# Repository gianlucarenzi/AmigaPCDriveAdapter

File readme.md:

# Amiga Floppy to PC Floppy Adapter

Created by Gianluca Renzi (C) 2018
 E-Mail:
- <icjtqr@gmail.com>
- <gianlucarenzi@eurek.it>

# PCB Revision History

- V0.1 Initial Revision 2018 Made with Kicad 4.x
- V1.0 First (BAD) PCB revision from transition from Kicad 4.x to Kicad 5.x
- V2.0 PCB Revision entirely made on Kicad 5. No library from Kicad 4 anymore.

# What is it?
It is a simple but powerful adapter to use internally in any Amiga Computer!
It must be connected to the floppy disk drive 34-pin interface on the drive
itself, then hooked up with the original cables from Amiga motherboard.

# Images

# What's changed?

- V0.1 Initial release (2018)
- V1.0 From Kicad 4 to Kicad 5 (2019). I found a bug in PCB version automatically generated by Kicad 5 from Kicad 4: All the hand soldering pads are way too large and they are overlapping each other short-circuiting every signal with a large series of resistors. Thanks to: __Stefan Gammelgaard(BM)__ to point me out on this issue.
- V2.0 Updated and Corrected for usage in Kicad 5 (2020)

# Bill of materials (from Digikey)

| Quantity | Digikey's Part No.           | Manufacturer's Part. No. | Description                   | PCB/Schematic's Reference   |
| -------- | -----------------------------| ------------------------ | ----------------------------- | --------------------------- |
|    2     | 445-10000-1-ND	              | CGA5H2X8R2A104K115AD	    | CAP CER 0.1UF 100V 1206 EPOXY |          C2, C3             |
|   10	    | P2.2KECT-ND	                 | ERJ-8GEYJ222V	           | RES SMD 2.2K OHM 5% 1/4W 1206 | R1, R2, R3, R4, R5, R6, R7  |
|    1	    | 754-APTR3216SECK/J3-PRVCT-ND | APTR3216SECK/J3-PRV	     | LED SMD	                      |             D1              |
|    1     | WM4002-ND                    |	0022032041	              | CONN HEADER VERT 4POS 2.54MM	 |             P1              |
|    1     | 609-3407-ND                  | 68016-404HLF             | CONN HEADER R/A 4POS 2.54MM   |             P2              |
|    1     | 541-CRCW1206330RJNEACCT-ND   | CRCW1206330RJNEAC        | RES 330 OHM 5% 1/4W 1206      |             R8              |
|    1     | S9174-ND                     | SBH11-PBPC-D17-ST-BK     | CONN HEADER VERT 34POS 2.54MM |          TO_AMIGA1          |
|    1     | ED3068-ND                    | SH2-34G-PT               | CONN RCPT 34POS 0.1 GOLD PCB  |          TO_FLOPPY1         |
|    1     | 296-1664-5-ND                | SN74LS38N                | IC GATE NAND 4CH 2-INP 14DIP  |             U1              |
|    2     | 478-10757-1-ND               | TPSA106K016R1000         | CAP TANT 10UF 10% 16V 1206    |           C1, C4            |

# Licence
This entire project is available under the GNU General Public License v3 licence.
See licence.txt for more details.

Additional Copyright/License
Permission is hereby granted, free of charge, to any person obtaining a copy of this software and associated documentation files (the "Software"), to deal in the Software without restriction, including without limitation the rights to use, copy, modify, merge, publish, distribute, sublicense, and/or sell copies of the Software, and to permit persons to whom the Software is furnished to do so, subject to the following conditions:

The above copyright notice and this permission notice shall be included in all copies or substantial portions of the Software/Hardware.

THE SOFTWARE/HARDWARE IS PROVIDED "AS IS", WITHOUT WARRANTY OF ANY KIND, EXPRESS OR IMPLIED, INCLUDING BUT NOT LIMITED TO THE WARRANTIES OF MERCHANTABILITY, FITNESS FOR A PARTICULAR PURPOSE AND NONINFRINGEMENT. IN NO EVENT SHALL THE AUTHORS OR COPYRIGHT HOLDERS BE LIABLE FOR ANY CLAIM, DAMAGES OR OTHER LIABILITY, WHETHER IN AN ACTION OF CONTRACT, TORT OR OTHERWISE, ARISING FROM, OUT OF OR IN CONNECTION WITH THE SOFTWARE/HARDWARE OR THE USE OR OTHER DEALINGS IN THE SOFTWARE/HARDWARE.

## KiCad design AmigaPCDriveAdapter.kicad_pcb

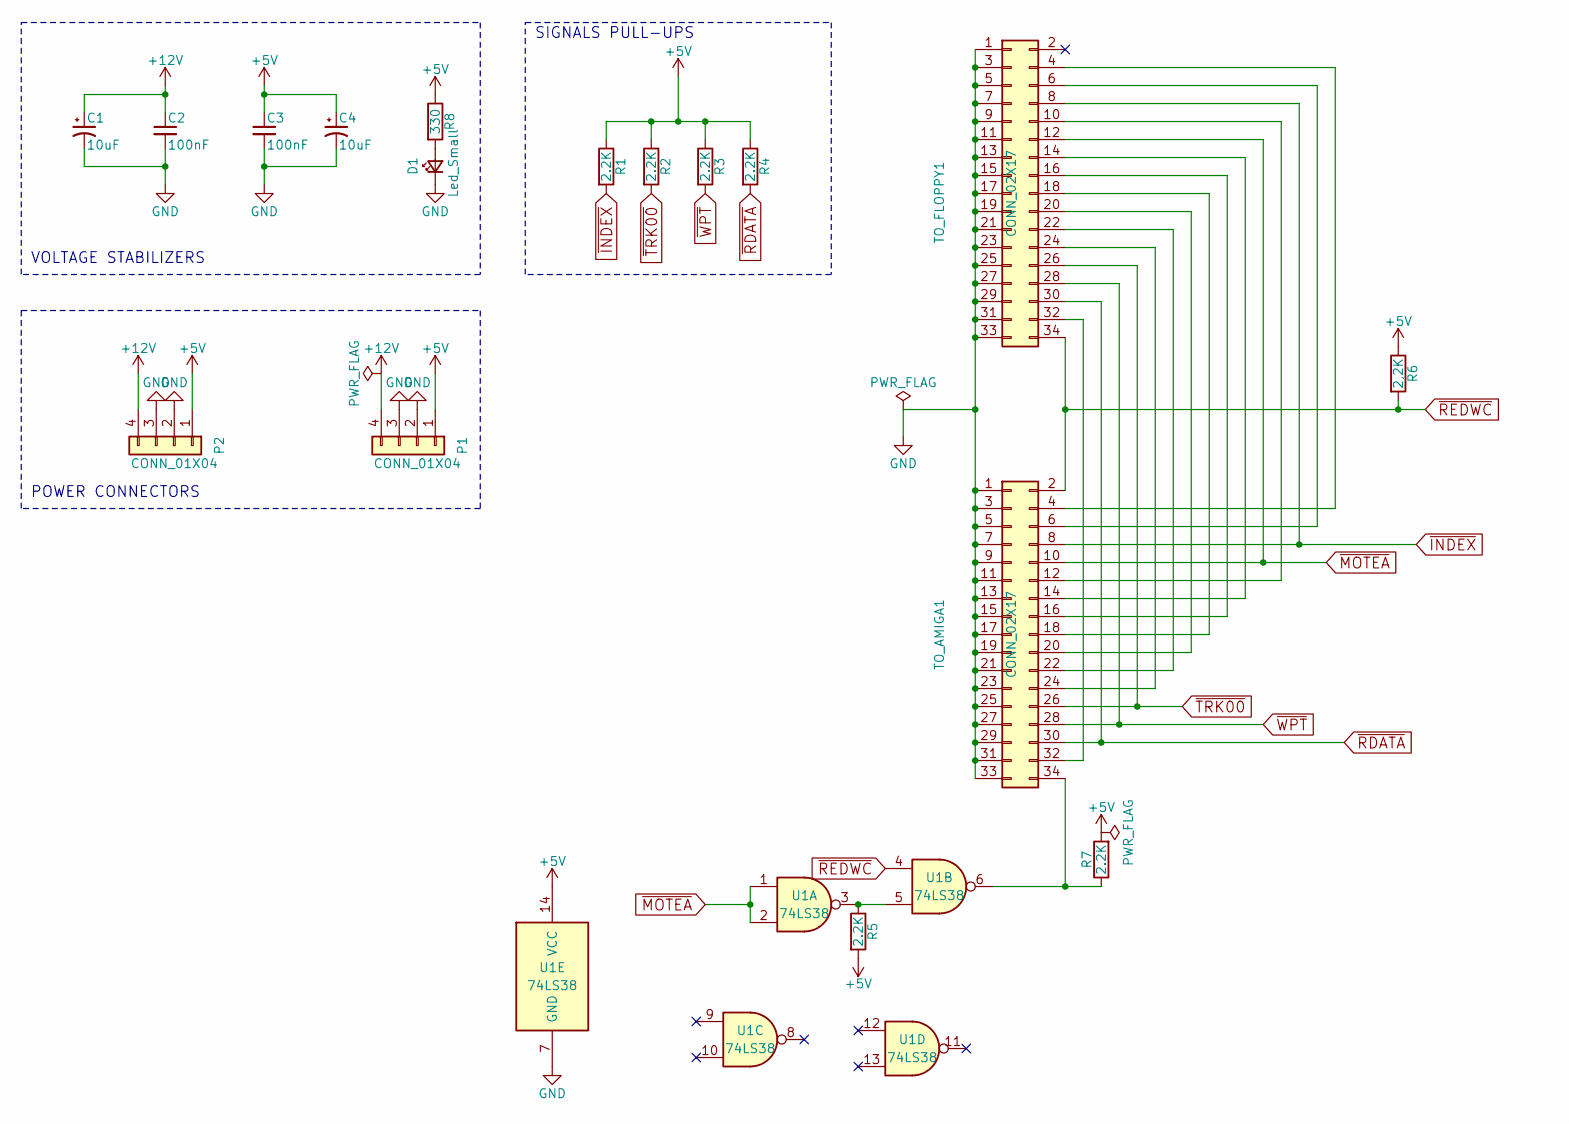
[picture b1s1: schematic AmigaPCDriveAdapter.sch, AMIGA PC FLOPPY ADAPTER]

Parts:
C1, C4: 10uF; CP_EIA-3216-12_Kemet-S
C2, C3: 100nF; C_1206_3216Metric_Pad1.33x1.80mm_HandSolder
D1: Led_Small; LED_1206_3216Metric_Pad1.42x1.75mm_HandSolder
P1: CONN_01X04; PinHeader_1x04_P2.54mm_Vertical
P2: CONN_01X04; PinHeader_1x04_P2.54mm_Horizontal
R1, R2, R3, R4, R5, R7: 2.2K; R_1206_3216Metric_Pad1.30x1.75mm_HandSolder
R6: 2,2K; R_1206_3216Metric_Pad1.30x1.75mm_HandSolder
R8: 330; R_1206_3216Metric_Pad1.30x1.75mm_HandSolder
TO_AMIGA1: CONN_02X17; IDC-Header_2x17_P2.54mm_Vertical_Lock
TO_FLOPPY1: CONN_02X17; PinSocket_2x17_P2.54mm_Vertical
U1: 74LS38; DIP-14_W7.62mm

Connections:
+5V: C3.1, C4.1, P1.1, P2.1, R1.1, R2.1, R3.1, R4.1, R5.2, R6.1, R7.2, R8.1, U1.14 (VCC)
+12V: C1.1, C2.1, P1.4, P2.4
GND: C1.2, C2.2, C3.2, C4.2, D1.1 (K), P1.2, P1.3, P2.2, P2.3, TO_AMIGA1.1, TO_AMIGA1.3, TO_AMIGA1.5, TO_AMIGA1.7, TO_AMIGA1.9, TO_AMIGA1.11, TO_AMIGA1.13, TO_AMIGA1.15, TO_AMIGA1.17, TO_AMIGA1.19, TO_AMIGA1.21, TO_AMIGA1.23, TO_AMIGA1.25, TO_AMIGA1.27, TO_AMIGA1.29, TO_AMIGA1.31, TO_AMIGA1.33, TO_FLOPPY1.1, TO_FLOPPY1.3, TO_FLOPPY1.5, TO_FLOPPY1.7, TO_FLOPPY1.9, TO_FLOPPY1.11, TO_FLOPPY1.13, TO_FLOPPY1.15, TO_FLOPPY1.17, TO_FLOPPY1.19, TO_FLOPPY1.21, TO_FLOPPY1.23, TO_FLOPPY1.25, TO_FLOPPY1.27, TO_FLOPPY1.29, TO_FLOPPY1.31, TO_FLOPPY1.33, U1.7 (GND)
unnamed: D1.2 (A), R8.2
unnamed: R5.1, U1.3, U1.5
unnamed: R7.1, TO_AMIGA1.34, U1.6
unnamed: TO_AMIGA1.4, TO_FLOPPY1.4
unnamed: TO_AMIGA1.6, TO_FLOPPY1.6
unnamed: TO_AMIGA1.12, TO_FLOPPY1.10
unnamed: TO_AMIGA1.14, TO_FLOPPY1.14
unnamed: TO_AMIGA1.16, TO_FLOPPY1.16
unnamed: TO_AMIGA1.18, TO_FLOPPY1.18
unnamed: TO_AMIGA1.20, TO_FLOPPY1.20
unnamed: TO_AMIGA1.22, TO_FLOPPY1.22
unnamed: TO_AMIGA1.24, TO_FLOPPY1.24
unnamed: TO_AMIGA1.32, TO_FLOPPY1.32
~INDEX: R1.2, TO_AMIGA1.8, TO_FLOPPY1.8
~MOTEA: TO_AMIGA1.10, TO_FLOPPY1.12, U1.1, U1.2
~RDATA: R4.2, TO_AMIGA1.30, TO_FLOPPY1.30
~REDWC: R6.2, TO_AMIGA1.2, TO_FLOPPY1.34, U1.4
~TRK00: R2.2, TO_AMIGA1.26, TO_FLOPPY1.26
~WPT: R3.2, TO_AMIGA1.28, TO_FLOPPY1.28

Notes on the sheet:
POWER CONNECTORS
VOLTAGE STABILIZERS
SIGNALS PULL-UPS

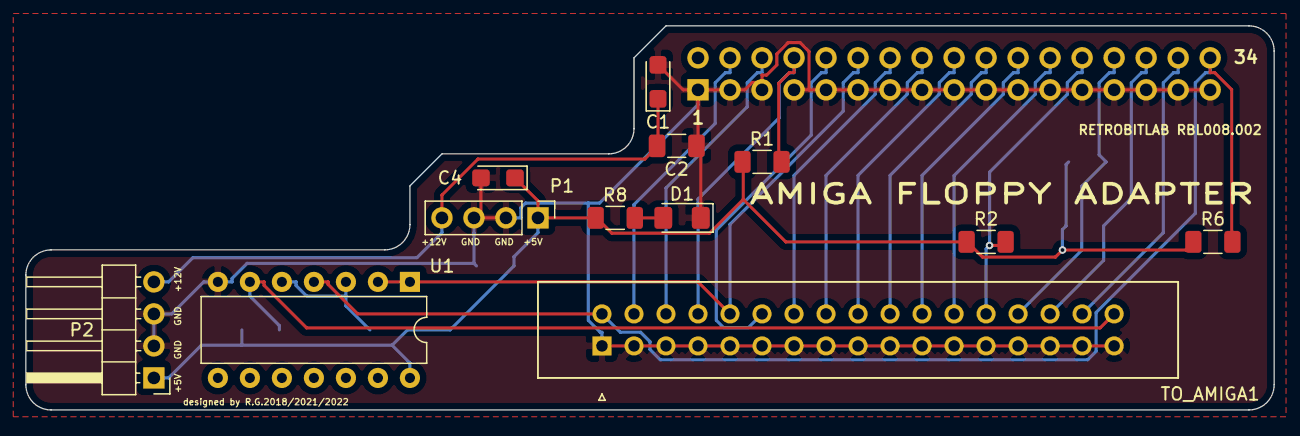
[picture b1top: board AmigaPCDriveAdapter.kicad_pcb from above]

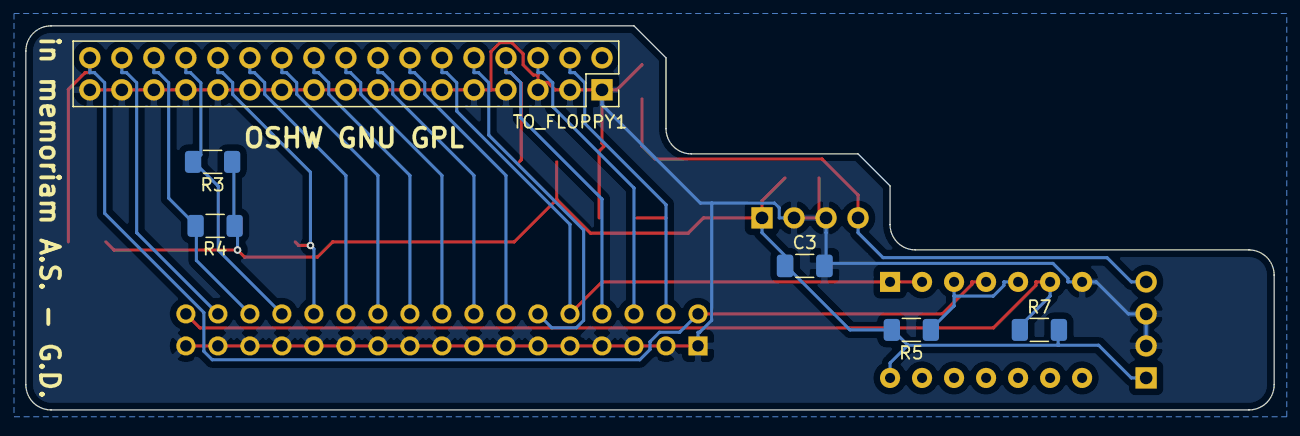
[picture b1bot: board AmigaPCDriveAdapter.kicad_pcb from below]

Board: 2 copper layers, 99.1 x 30.5 mm, 18 parts (6 on the bottom side), 22 nets.

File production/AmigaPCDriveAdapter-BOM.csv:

"Id";"Designator";"Package";"Quantity";"Designation";"Supplier and ref";
1;"U1";"DIP-14_W7.62mm";1;"74LS38";;;
2;"C1,C4";"CP_EIA-3216-12_Kemet-S";2;"10uF";;;
3;"C2,C3";"C_1206_3216Metric_Pad1.42x1.75mm_HandSolder";2;"100nF";;;
4;"D1";"LED_1206_3216Metric_Pad1.42x1.75mm_HandSolder";1;"Led_Small";;;
5;"P1";"PinHeader_1x04_P2.54mm_Vertical";1;"CONN_01X04";;;
6;"P2";"PinHeader_1x04_P2.54mm_Horizontal";1;"CONN_01X04";;;
7;"R1,R2,R3,R4,R5,R7";"R_1206_3216Metric_Pad1.42x1.75mm_HandSolder";6;"2.2K";;;
8;"R6";"R_1206_3216Metric_Pad1.42x1.75mm_HandSolder";1;"2,2K";;;
9;"R8";"R_1206_3216Metric_Pad1.42x1.75mm_HandSolder";1;"330";;;
10;"TO_AMIGA1";"IDC-Header_2x17_P2.54mm_Vertical_Lock";1;"CONN_02X17";;;
11;"TO_FLOPPY1";"PinSocket_2x17_P2.54mm_Vertical";1;"CONN_02X17";;;
12;"OSHW";"OSHW-Logo_5.7x6mm_SilkScreen";1;"OSHW-Logo_5.7x6mm_SilkScreen";;;

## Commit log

2018-12-23 First Import in Git
2018-12-23 removed
2019-01-06 Modified libraries path
2019-01-06 Modified library path
2019-01-20 Added after a library update
2019-01-20 Update libraries
2019-01-20 added .gitignore
2019-02-14 Added licence GPL v3
2019-02-14 Added images
2019-02-14 Another image
2019-02-14 3rd try
2019-03-01 Correct some library issues. Part ONE
2019-03-01 Correct some libraries issues. Part TWO
2019-03-01 Automatically Generated
2019-03-01 Added board overall
2019-06-17 Modified in VM x86
2019-06-17 Added BOM (generated from PCB)
2021-01-23 Added after update the schematics for Kicad 5 from Kicad 4
2021-01-23 Version Kicad 5 V2.0
2021-01-23 Added from Kicad 5
2021-01-23 Updated to drop the rescue file
2021-01-23 Changed version due to a hw BUG.
2021-01-23 Update from PCB_NEW Kicad 5
2021-01-23 Gerber Files for Production v2.0
2021-01-23 DigiKey-ShoppingCart
2021-01-23 Modified TANTALUM Cap for a more common type.
2021-01-25 Update readme.md
    Grammar spelling checker! ;-)
2022-04-01 Generated with latest version of KiCAD 5.1.9

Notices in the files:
AmigaPCDriveAdapter.kicad_pcb:
OSHW GNU GPL
